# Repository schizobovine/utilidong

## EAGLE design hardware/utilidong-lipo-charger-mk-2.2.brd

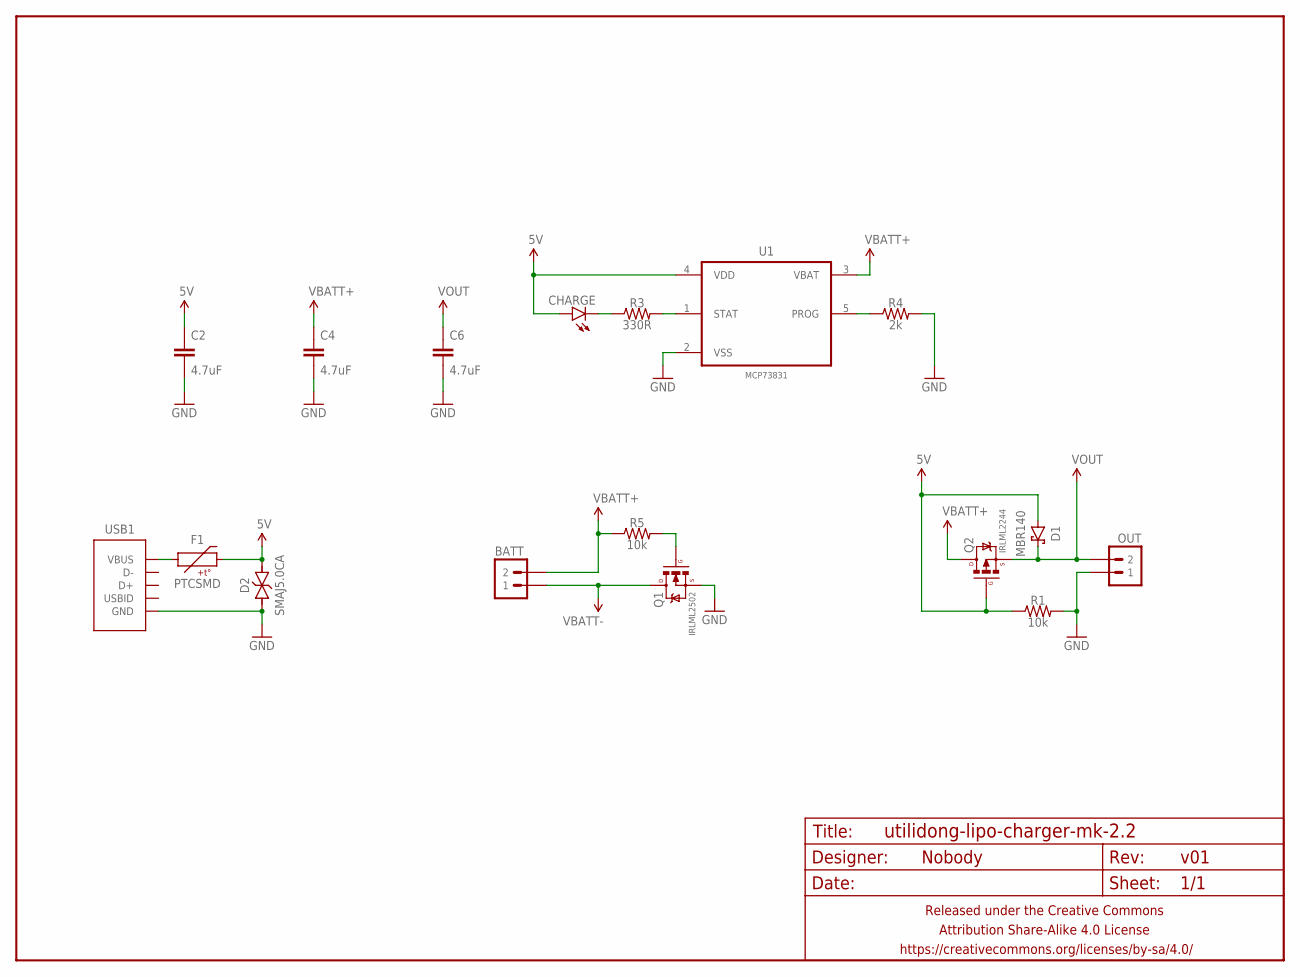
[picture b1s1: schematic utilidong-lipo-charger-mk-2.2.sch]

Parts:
BATT: M02PTH-CENTERED-R+; 1X02-CENTER-R+
C2, C4, C6: 4.7uF; C0603
CHARGE: LED1206; LED-1206
D1: MBR140; SMA-DIODE-SCHOTTKY
D2: SMAJ5.0CA; SMA-DIODE-TVS-BIDIR
F1: PTCSMD; PTC-1206
FRAME1: FRAME-LETTERNO_PACKAGE; DUMMY
OUT: M02PTH-CENTERED-R+; 1X02-CENTER-R+
Q1: IRLML2502; SOT23
Q2: IRLML2244; SOT23-3
R1, R5: 10k; R0603
R3: 330R; R0603
R4: 2k; R0603
U1: MCP73831; SOT95P280X145-5N
USB1: USB-ABCOMBO; USB-MICRO-B-FCI-CUTOUT

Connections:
5V: C2.1, CHARGE.A, D1.A, D2.2, F1.2, Q2.1 (G), R1.1, U1.4 (VDD)
GND: C2.2, C4.2, C6.2, D2.1, OUT.1, Q1.2 (S), R1.2, R4.2, U1.2 (VSS), USB1.5 (GND), USB1.P$1 (GND), USB1.P$2 (GND)
unnamed: R3.2, U1.1 (STAT)
unnamed: CHARGE.C, R3.1
unnamed: R4.1, U1.5 (PROG)
unnamed: Q1.1 (G), R5.2
VBATT+: BATT.2, C4.1, Q2.3 (D), R5.1, U1.3 (VBAT)
VBATT-: BATT.1, Q1.3 (D)
VBUS: F1.1, USB1.1 (VBUS)
VOUT: C6.1, D1.C, OUT.2, Q2.2 (S)

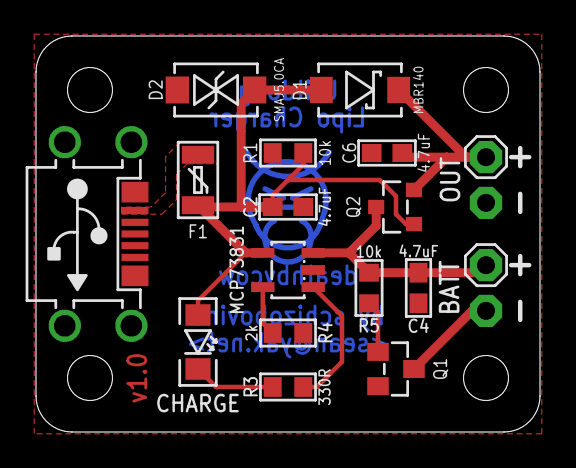
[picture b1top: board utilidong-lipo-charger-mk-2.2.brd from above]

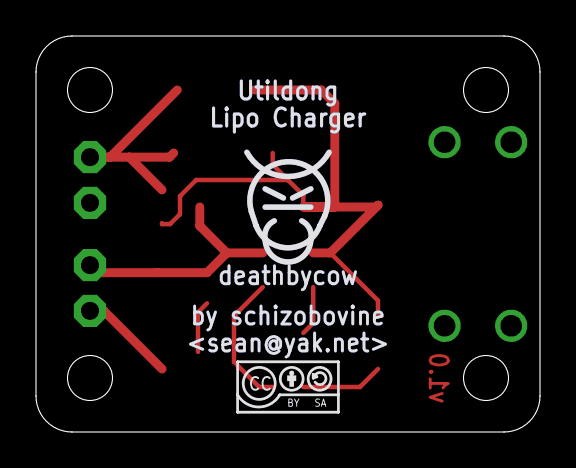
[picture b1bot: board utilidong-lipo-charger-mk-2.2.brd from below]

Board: 2 copper layers, 28.0 x 22.0 mm, 20 parts (2 on the bottom side), 10 nets.

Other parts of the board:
U$8: CC-BY-SA-4.0-NO-URL
U$9: COW_SMALL_METAL

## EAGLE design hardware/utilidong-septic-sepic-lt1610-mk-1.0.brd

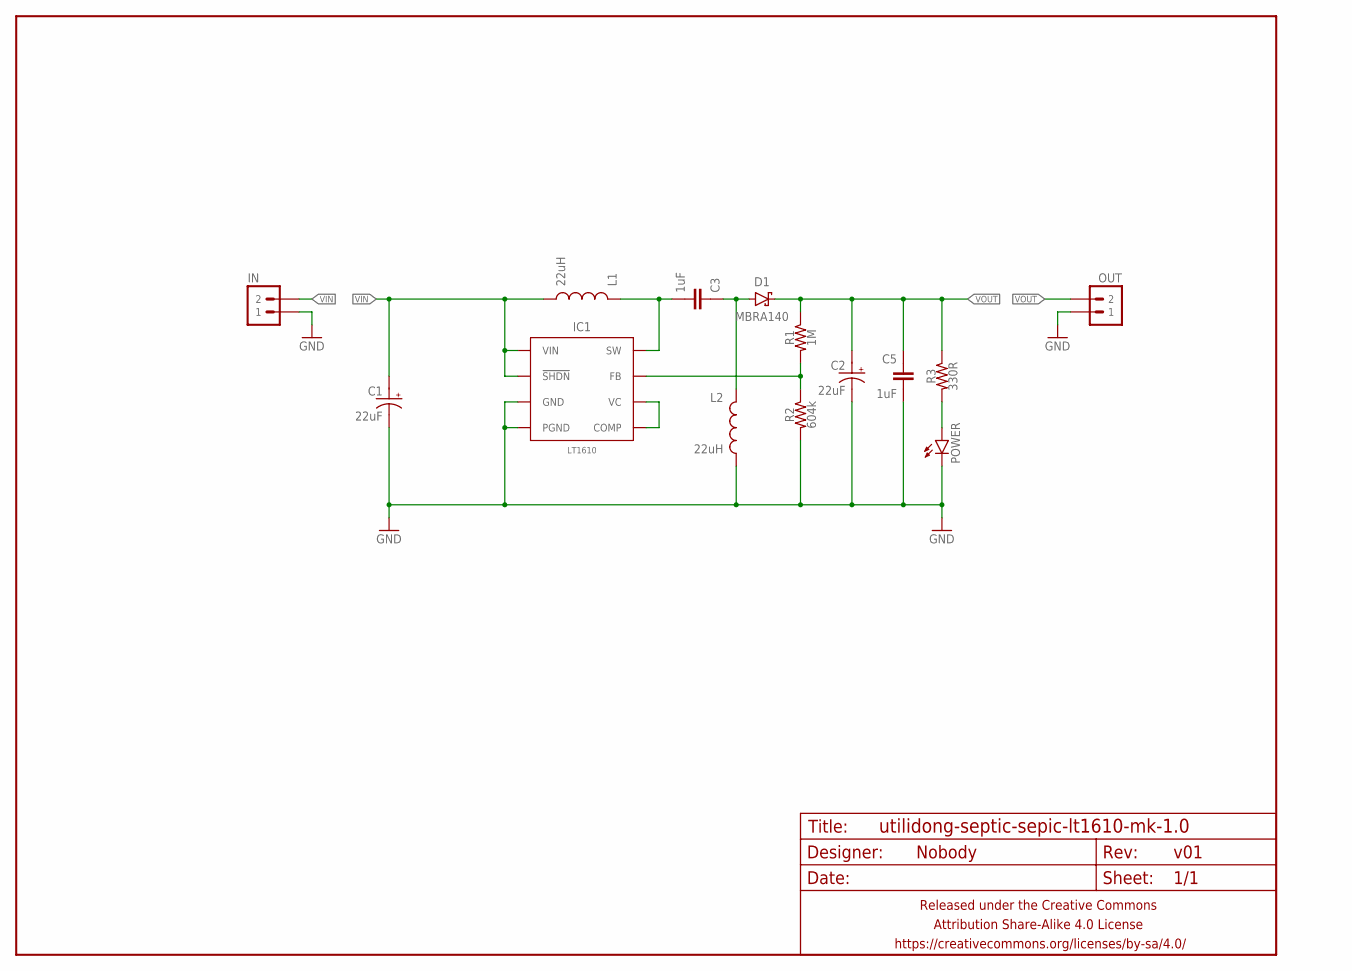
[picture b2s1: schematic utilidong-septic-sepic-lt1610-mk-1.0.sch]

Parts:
C1, C2: 22uF; E2,5-6
C3, C5: 1uF; C0805
D1: MBRA140; SMA-DIODE-SCHOTTKY
FRAME1: FRAME-LETTERNO_PACKAGE; DUMMY
IC1: LT1610; SO08
IN: M02PTH-CENTERED-R+; 1X02-CENTER-R+
L1, L2: 22uH; TAIYO-YUDEN-40XX
OUT: M02PTH-CENTERED-R+; 1X02-CENTER-R+
POWER: LED1206; LED-1206
R1: 1M; R0805
R2: 604k; R0805
R3: 330R; R0805

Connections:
GND: C1.-, C2.-, C5.2, IC1.4 (PGND), IC1.7 (GND), IN.1, L2.2, OUT.1, POWER.C, R2.2
unnamed: POWER.A, R3.2
unnamed: C3.2, IC1.5 (SW), L1.1
unnamed: IC1.1 (VC), IC1.8 (COMP)
unnamed: C3.1, D1.A, L2.1
unnamed: IC1.2 (FB), R1.2, R2.1
VIN: C1.+, IC1.3 (!SHDN), IC1.6 (VIN), IN.2, L1.2
VOUT: C2.+, C5.1, D1.C, OUT.2, R1.1, R3.1

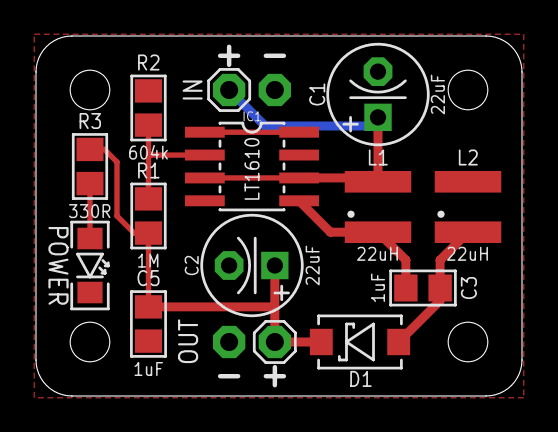
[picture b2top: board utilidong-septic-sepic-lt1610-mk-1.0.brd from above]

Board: 2 copper layers, 27.0 x 20.0 mm, 15 parts (0 on the bottom side), 8 nets.

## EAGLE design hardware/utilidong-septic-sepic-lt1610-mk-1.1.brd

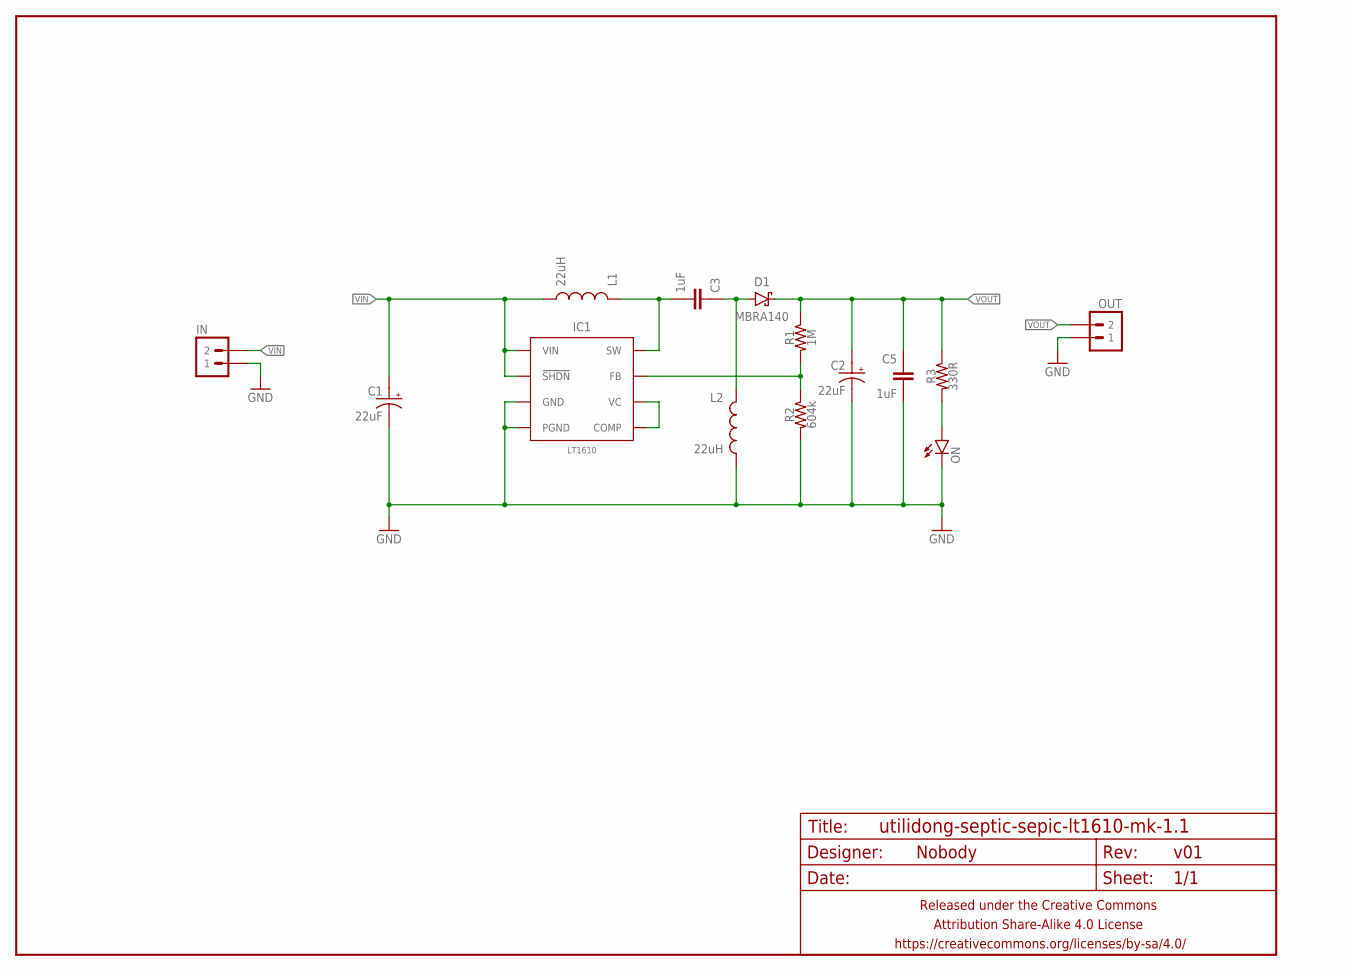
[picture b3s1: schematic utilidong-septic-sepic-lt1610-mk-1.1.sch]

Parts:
C1, C2: 22uF; E2,5-6
C3, C5: 1uF; C0805
D1: MBRA140; SMA-DIODE
FRAME1: FRAME-LETTERNO_PACKAGE; DUMMY
IC1: LT1610; SO08
IN: M02PTH-CENTERED-R+; 1X02-CENTER-R+
L1, L2: 22uH; MURATA-1100R
ON: LED3MM-LESS; LED3MM-LESSSILK
OUT: M02PTH-CENTERED-R+; 1X02-CENTER-R+
R1: 1M; R0805
R2: 604k; R0805
R3: 330R; R0805

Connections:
GND: C1.-, C2.-, C5.2, IC1.4 (PGND), IC1.7 (GND), IN.1, L2.P$2 (2), ON.K (C), OUT.1, R2.2
unnamed: ON.A, R3.2
unnamed: C3.2, IC1.5 (SW), L1.P$1 (1)
unnamed: IC1.1 (VC), IC1.8 (COMP)
unnamed: C3.1, D1.A, L2.P$1 (1)
unnamed: IC1.2 (FB), R1.2, R2.1
VIN: C1.+, IC1.3 (!SHDN), IC1.6 (VIN), IN.2, L1.P$2 (2)
VOUT: C2.+, C5.1, D1.C, OUT.2, R1.1, R3.1

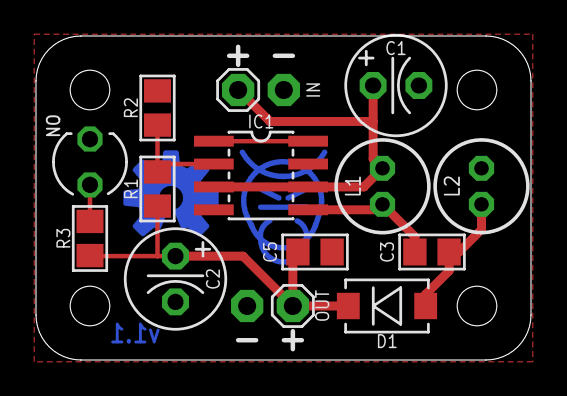
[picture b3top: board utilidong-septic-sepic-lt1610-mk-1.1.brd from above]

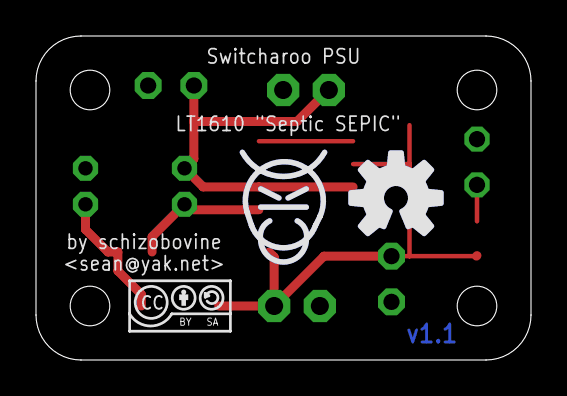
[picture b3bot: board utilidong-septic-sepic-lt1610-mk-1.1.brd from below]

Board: 2 copper layers, 27.5 x 18.0 mm, 18 parts (3 on the bottom side), 8 nets.

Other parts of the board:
U$1: CC-BY-SA-4.0-NO-URL
U$2: COW_SMALL_METAL_NOTEXT
U$3: OSHWLOGO_TOP_0.2_A

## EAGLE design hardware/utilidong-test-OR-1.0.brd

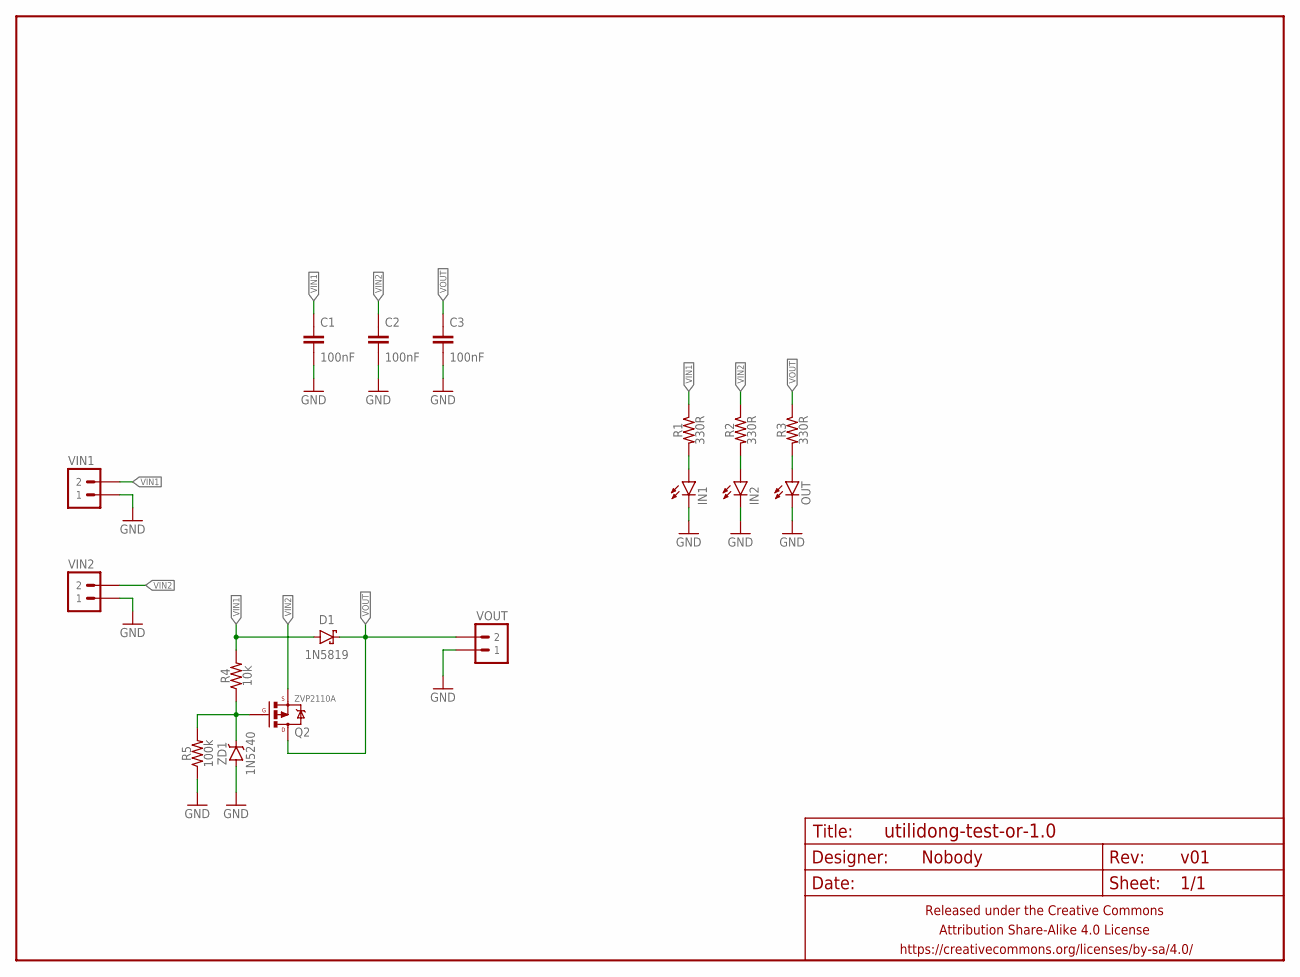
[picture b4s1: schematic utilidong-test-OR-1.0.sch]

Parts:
C1, C2, C3: 100nF; C025-024X044
D1: 1N5819; DIODE-7.62MM
FRAME1: FRAME-LETTERNO_PACKAGE; DUMMY
IN1, IN2: LED3MM-LESS; LED3MM-LESSSILK
OUT: LED3MM-LESS; LED3MM-LESSSILK
Q2: ZVP2110A; TO-92-AMMO
R1, R2, R3: 330R; RESISTOR-AXIAL-PTH-7.62MM
R4: 10k; RESISTOR-AXIAL-PTH-7.62MM
R5: 100k; RESISTOR-AXIAL-PTH-7.62MM
VIN1, VIN2: M02PTH-CENTERED-R+; 1X02-CENTER-R+
VOUT: M02PTH-CENTERED-R+; 1X02-CENTER-R+
ZD1: 1N5240; DIODE-7.62MM

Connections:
GND: C1.2, C2.2, C3.2, IN1.K (C), IN2.K (C), OUT.K (C), R5.P$1 (1), VIN1.1, VIN2.1, VOUT.1, ZD1.A
unnamed: IN2.A, R2.P$2 (2)
unnamed: OUT.A, R3.P$2 (2)
unnamed: IN1.A, R1.P$2 (2)
unnamed: Q2.2 (G), R4.P$1 (1), R5.P$2 (2), ZD1.K (C)
VIN1: C1.1, D1.A, R1.P$1 (1), R4.P$2 (2), VIN1.2
VIN2: C2.1, Q2.3 (S), R2.P$1 (1), VIN2.2
VOUT: C3.1, D1.K (C), Q2.1 (D), R3.P$1 (1), VOUT.2

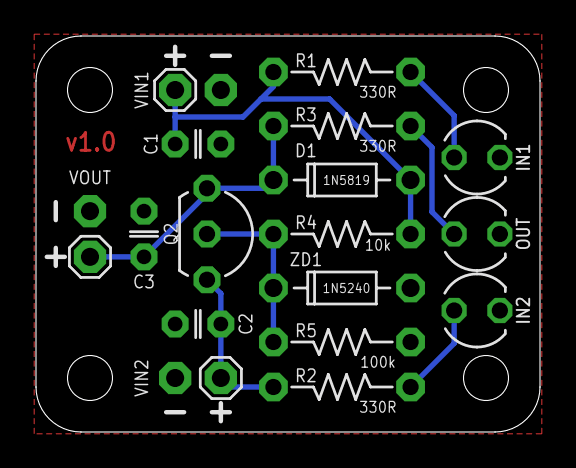
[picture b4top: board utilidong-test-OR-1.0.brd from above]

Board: 2 copper layers, 28.0 x 22.0 mm, 19 parts (1 on the bottom side), 8 nets.

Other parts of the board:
U$8: CC-BY-SA-4.0-NO-URL

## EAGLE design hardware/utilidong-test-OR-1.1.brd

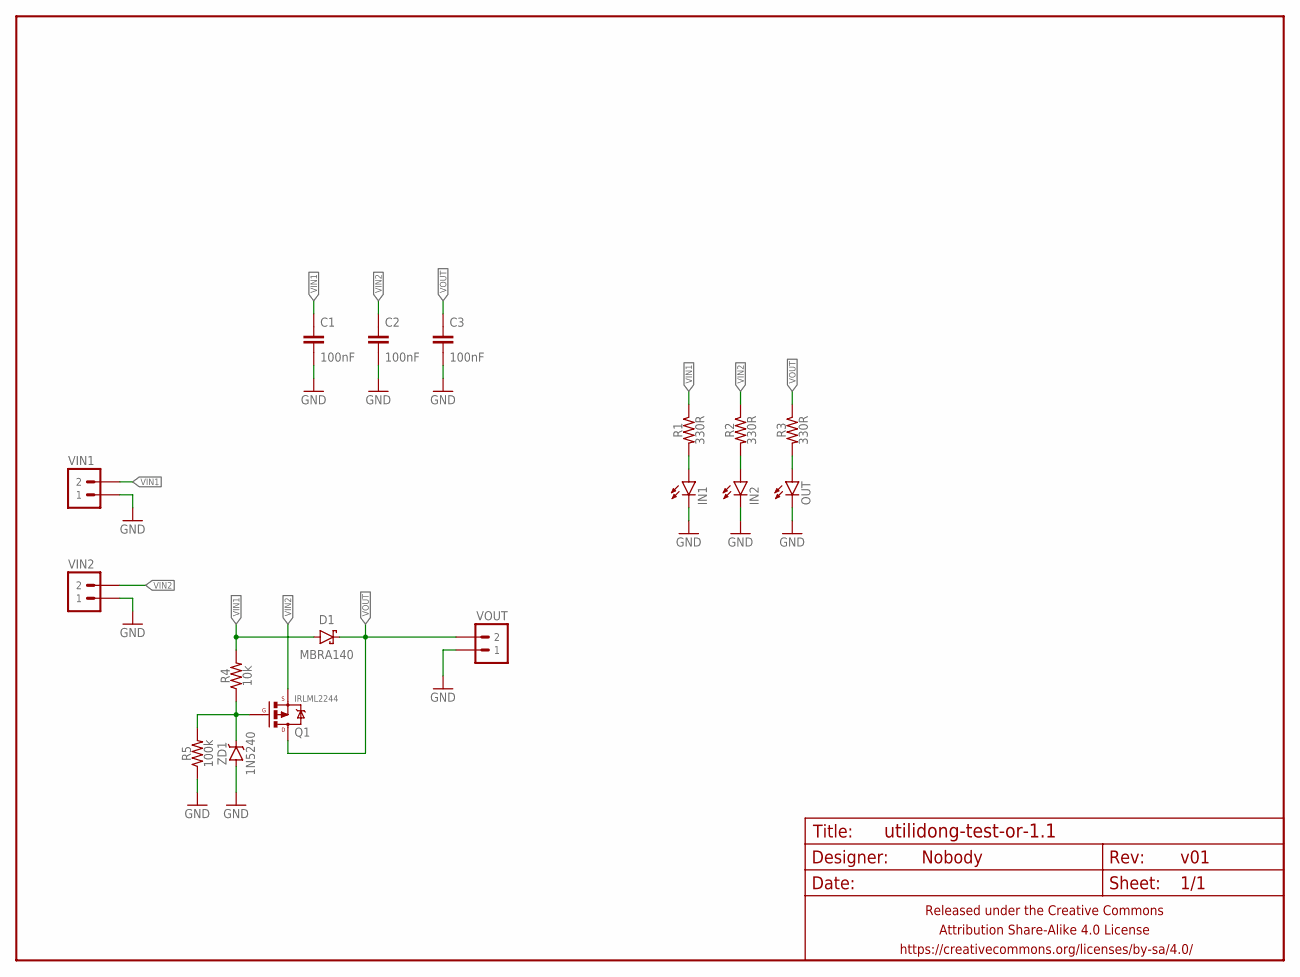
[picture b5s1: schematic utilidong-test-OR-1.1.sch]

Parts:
C1, C2, C3: 100nF; C0805
D1: MBRA140; SMA-DIODE
FRAME1: FRAME-LETTERNO_PACKAGE; DUMMY
IN1, IN2: LED1206; LED-1206
OUT: LED1206; LED-1206
Q1: IRLML2244; SOT23
R1, R2, R3: 330R; R0805
R4: 10k; R0805
R5: 100k; R0805
VIN1, VIN2: M02PTH-CENTERED-R+; 1X02-CENTER-R+
VOUT: M02PTH-CENTERED-R+; 1X02-CENTER-R+
ZD1: 1N5240; SOT23

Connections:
GND: C1.2, C2.2, C3.2, IN1.C, IN2.C, OUT.C, R5.1, VIN1.1, VIN2.1, VOUT.1, ZD1.1 (A), ZD1.2 (A)
unnamed: IN2.A, R2.2
unnamed: OUT.A, R3.2
unnamed: IN1.A, R1.2
unnamed: Q1.1 (G), R4.1, R5.2, ZD1.3 (C)
VIN1: C1.1, D1.A, R1.1, R4.2, VIN1.2
VIN2: C2.1, Q1.2 (S), R2.1, VIN2.2
VOUT: C3.1, D1.C, Q1.3 (D), R3.1, VOUT.2

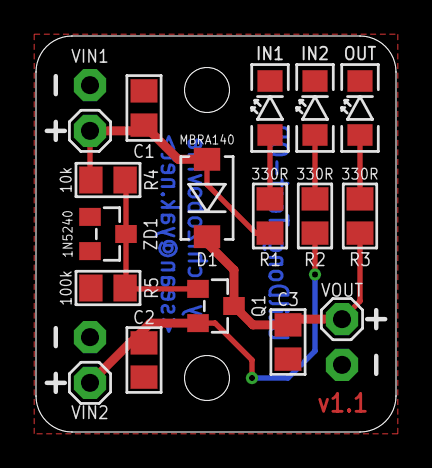
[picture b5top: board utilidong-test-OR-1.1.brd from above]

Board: 2 copper layers, 20.0 x 22.0 mm, 19 parts (1 on the bottom side), 8 nets.

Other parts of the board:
U$8: CC-BY-SA-4.0-NO-URL

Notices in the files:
parts and their libraries:
A_butts: Released under the Creative Commons Attribution Share-Alike 4.0 License
A_butts: https://creativecommons.org/licenses/by-sa/4.0
A_butts: Released under the Creative Commons
